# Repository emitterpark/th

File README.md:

**LoRaWAN Outdoor Temperature & Humidity Sensor**

**SENSOR**

**Temperature;**

Range -40 to +125 C

Resolution 0.01 C

Accuracy tolerance +-0.2 C

**Humidity;**

Range 0 to 100 %RH

Resolution 0.01 %RH

Accuracy tolerance +-2 %RH

High and Low Alarms with hysteresis

**RADIO**

LoRaWAN Class A

Licence Free ISM Bands (EU868, US915..), Default EU868, 8 Channel

Up to 100mW (20dbm) output power

High sensitivity -148dbm

3dbi External Antenna

Long Range, greater than 10km line of sight

**POWER**

3.6V 9000mah ER26500 C Size LiSClO2

15uA sleep current

Up to 5 years battery life depending on send interval

Low battery alarm

**CONFIGURATION**

Configuration via USB, Pc, Phone, Tablet

Send Interval, 5min to 24h

High and Low Alarm thresholds

Full LoRaWAN parameters access

Over The Air Activation (OTAA) with DevEUI, AppEUI, AppKEY

**PHYSICAL**

Outdoor IP65 waterproof enclosure

Mounting flanges

76X70X40mm

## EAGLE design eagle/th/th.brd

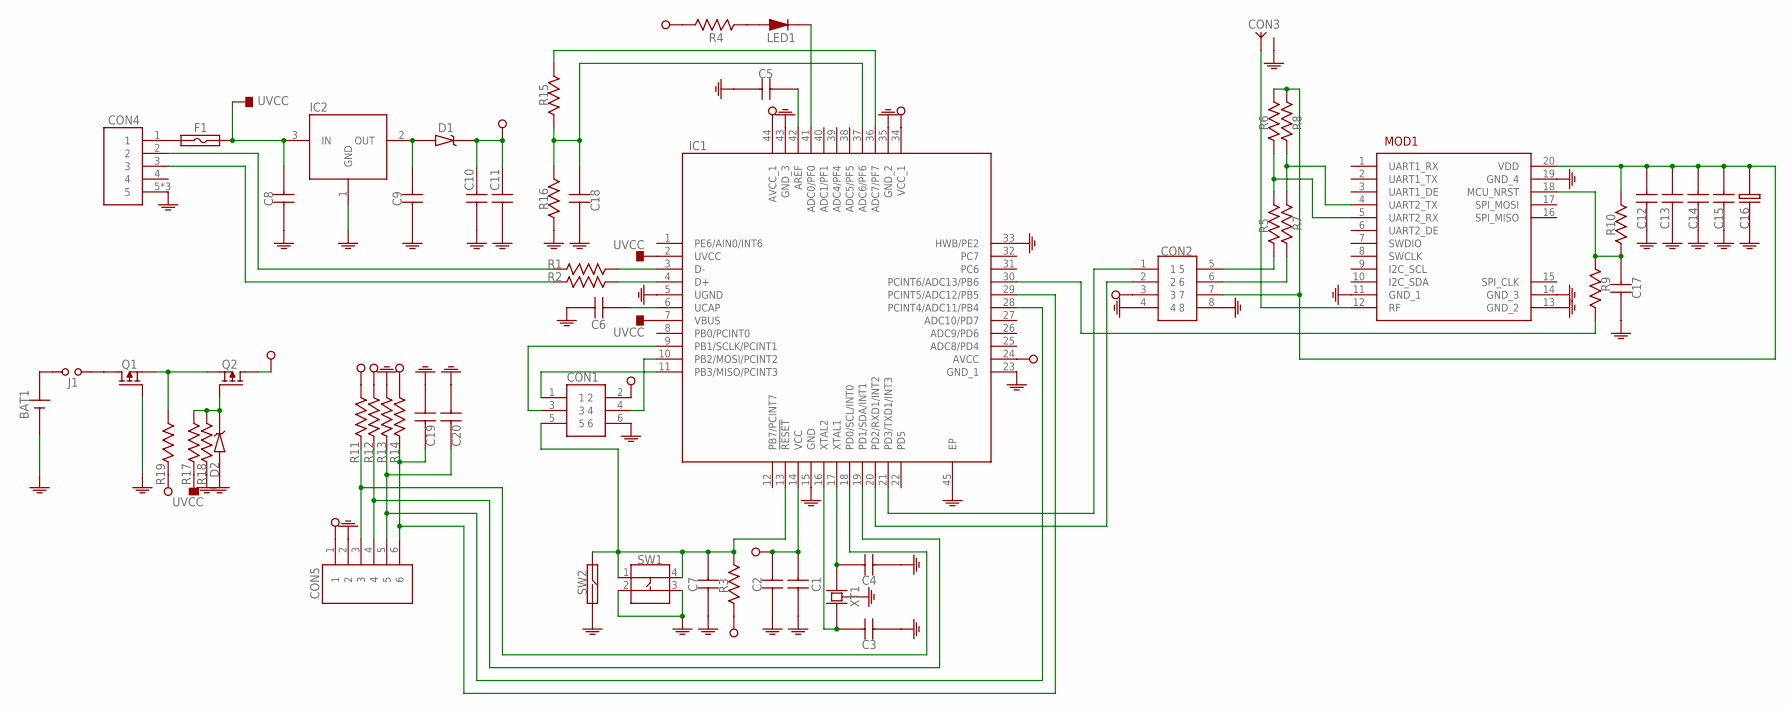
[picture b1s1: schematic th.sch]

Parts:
BAT1: 211P-C-HOLDER
C1, C2, C3, C4, C5, C6, C7, C10, C11, C12, C13, C14, C15, C17, C18, C19, C20: CAPACITOR-0603; 0603
C8, C9: CAPACITOR-0805; 0805
C16: CAPACITOR-10-5
CON1: ISP
CON2: HEADER-8P-2R-DIP-2_54MM
CON3: SMA-RF
CON4: USB-MICRO-DIP-VER
CON5: HEADER-6P-DIP-2_54MM
D1: DIODE-SCHOTTKY; SOD123-DIODE
D2: ZENER-SOD123; SOD123-DIODE
F1: FUSE-1206; 1206
IC1: ATMEGA32U4-MU; QFN-44
IC2: VREG-SOT23-3; SOT23-3
J1: JUMPER; HEADER-2P-DIP-2_54MM
LED1: LED-0805; 0805-LED
MOD1: RAK4200
Q1, Q2: P-MOSFET; SOT23-3
R1, R2, R3, R4, R5, R6, R7, R8, R9, R10, R11, R12, R13, R14, R15, R16, R17, R18, R19: RESISTOR-0603; 0603
SW1: BUTTON-4P-SMD-5X5
SW2: REED-DIP
XT1: CRYSTAL-5032-4P

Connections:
GND: BAT1.2 (-), C1.1, C2.1, C3.1, C4.1, C5.1, C6.1, C7.1, C8.1, C9.1, C10.1, C11.1, C12.1, C13.1, C14.1, C15.1, C16.P$1 (1), C17.1, C18.1, C19.1, C20.1, CON1.6, CON2.4, CON2.8, CON3.2 (GND), CON3.3 (GND), CON3.4 (GND), CON3.5 (GND), CON4.5, CON4.6 (5), CON4.7 (5), CON5.2, D2.2 (A), IC1.5 (UGND), IC1.15 (GND), IC1.23 (GND_1), IC1.33 (HWB/PE2), IC1.35 (GND_2), IC1.43 (GND_3), IC1.45 (EP), IC2.1 (GND), MOD1.11 (GND_1), MOD1.13 (GND_2), MOD1.14 (GND_3), MOD1.19 (GND_4), Q1.1 (G), R13.1, R16.1, R18.1, SW1.2, SW1.3, SW2.P$2 (2), XT1.2 (GND), XT1.4 (GND)
unnamed: C7.2, CON1.5, IC1.13 (!RESET), R3.2, SW1.1, SW1.4, SW2.P$1 (1)
unnamed: C17.2, MOD1.18 (MCU_NRST), R9.1, R10.1
unnamed: CON1.1, IC1.11 (PB3/MISO/PCINT3)
unnamed: CON3.1 (ANT), MOD1.12 (RF)
unnamed: J1.1, Q1.3 (D)
unnamed: CON2.5, R5.1
unnamed: CON2.6, R7.1
unnamed: BAT1.1 (+), J1.2 (3)
unnamed: CON1.4, IC1.10 (PB2/MOSI/PCINT2)
unnamed: C3.2, IC1.16 (XTAL2), XT1.1
unnamed: CON2.2, IC1.20 (PD2/RXD1/INT2)
unnamed: C4.2, IC1.17 (XTAL1), XT1.3 (2)
unnamed: IC1.41 (ADC0/PF0), LED1.1 (K)
unnamed: C20.2, CON5.5, IC1.28 (PCINT4/ADC11/PB4), R13.2
unnamed: C9.2, D1.2 (A), IC2.2 (OUT)
unnamed: IC1.30 (PCINT6/ADC13/PB6), R9.2
unnamed: CON4.2, R1.1
unnamed: IC1.3 (D-), R1.2
unnamed: IC1.4 (D+), R2.2
unnamed: C18.2, IC1.37 (ADC6/PF6), R15.2, R16.2
unnamed: D2.1 (K), Q2.1 (G), R17.2, R18.2
unnamed: C12.2, C13.2, C14.2, C15.2, C16.P$2 (2), CON2.7, MOD1.20 (VDD), R6.2, R8.2, R10.2
unnamed: CON2.1, IC1.21 (PD3/TXD1/INT3)
unnamed: CON4.3, R2.1
unnamed: C19.2, CON5.6, IC1.29 (PCINT5/ADC12/PB5), R14.2
unnamed: Q1.2 (S), Q2.2 (S), R19.2
unnamed: MOD1.4 (UART2_TX), R7.2, R8.1
unnamed: C5.2, IC1.42 (AREF)
unnamed: MOD1.5 (UART2_RX), R5.2, R6.1
unnamed: CON4.1, F1.1
unnamed: C6.2, IC1.6 (UCAP)
unnamed: LED1.2 (A), R4.1
unnamed: IC1.36 (ADC7/PF7), R15.1
unnamed: CON1.3, IC1.9 (PB1/SCLK/PCINT1)
unnamed: CON5.3, IC1.18 (PD0/SCL/INT0), R11.2
unnamed: CON5.4, IC1.19 (PD1/SDA/INT1), R12.2
UVCC: C8.2, F1.2, IC1.2 (UVCC), IC1.7 (VBUS), IC2.3 (IN), R17.1
VCC: C1.2, C2.2, C10.2, C11.2, CON1.2, CON2.3, CON5.1, D1.1 (K), IC1.14 (VCC), IC1.24 (AVCC), IC1.34 (VCC_1), IC1.44 (AVCC_1), Q2.3 (D), R3.1, R4.2, R11.1, R12.1, R14.1, R19.1

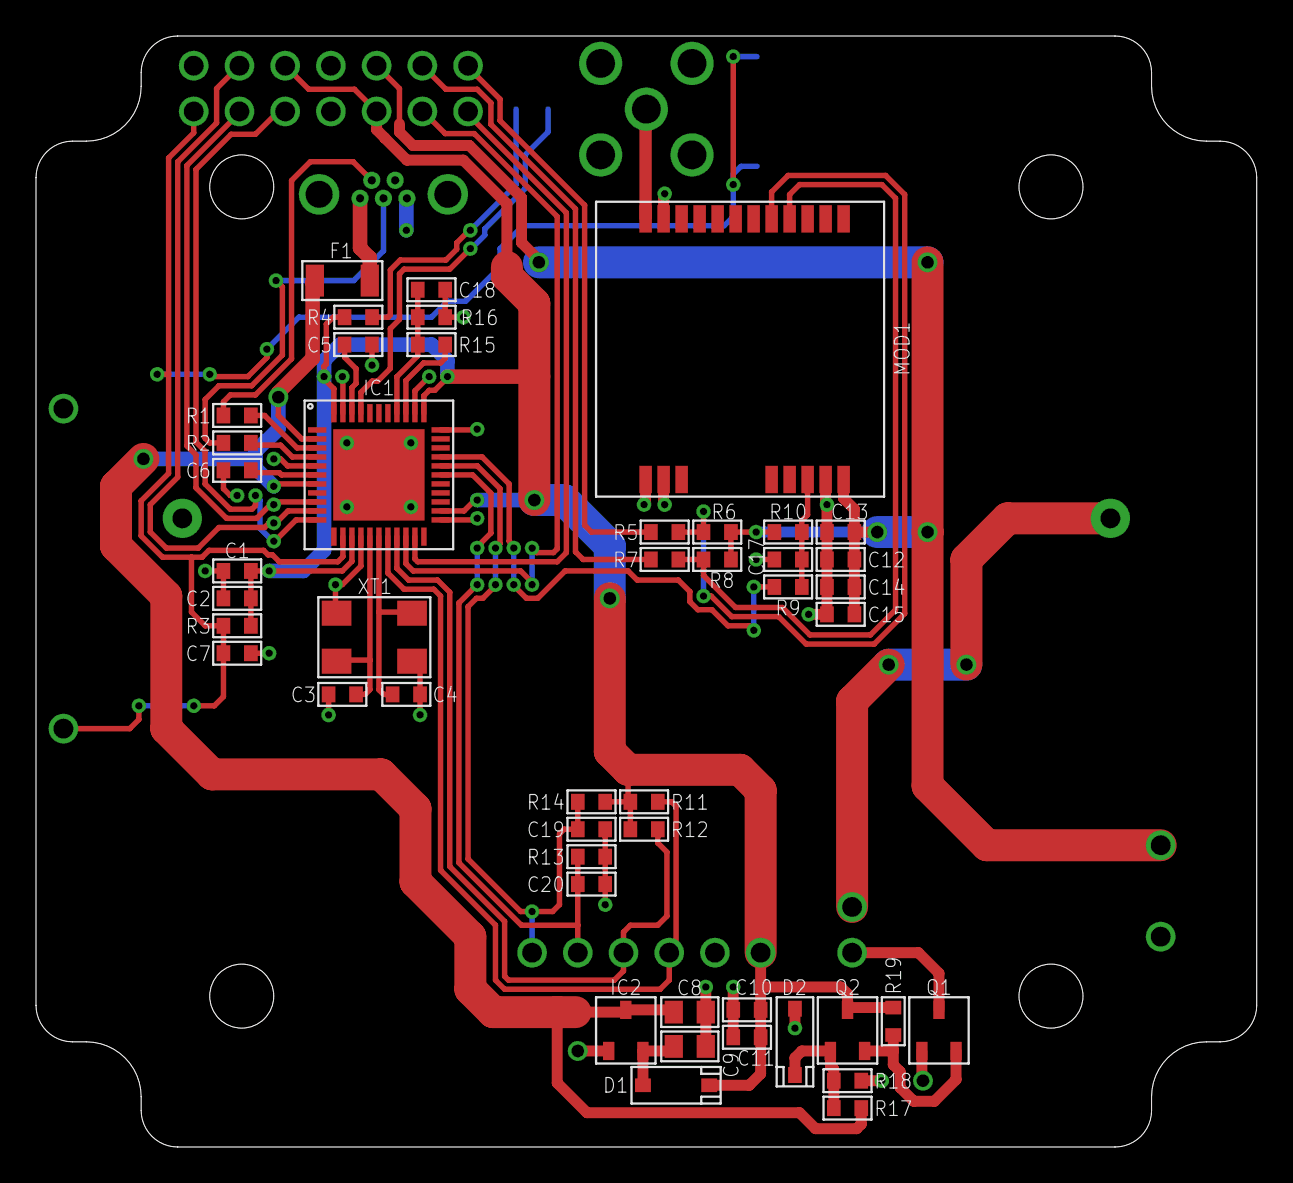
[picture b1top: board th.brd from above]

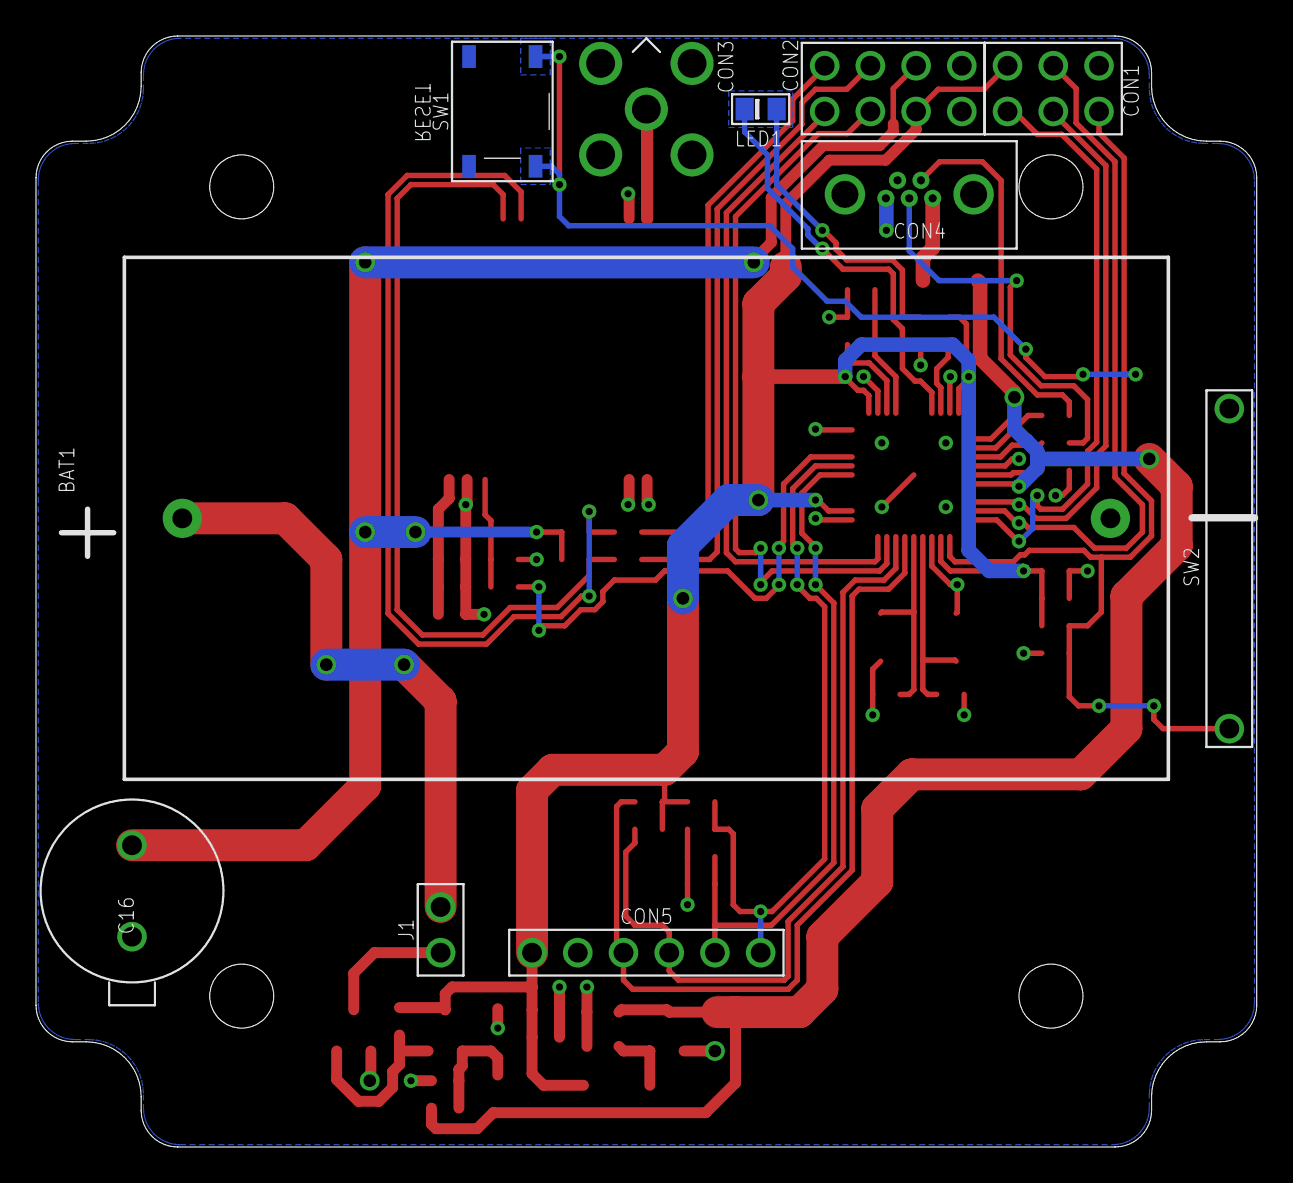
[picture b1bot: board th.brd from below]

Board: 2 copper layers, 67.8 x 61.7 mm, 58 parts (11 on the bottom side), 39 nets.

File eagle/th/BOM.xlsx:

IC1 | 1 | ATMEGA32U4-MU | QFN-44
IC2 | 1 | MCP1700T-3602E/TT | SOT23-3
MOD1 | 1 | RAK4200 LORA MODULE EU868MHZ | SM-20 | link
Q1,2 | 2 | SI2301BDS | SOT23-3
D1 | 1 | B5817W (MBR120) | SOD123
D2 | 1 | BZT52C3V9 | SOD123
LED1 | 1 | LED RED | 0805
XT1 | 1 | CRYSTAL PASSIVE 8MHZ 4PIN | 5032
F1 | 1 | PTC RESETTABLE FUSE 0.5A | 1206
SW1 | 1 | PUSH BUTTON 5.2X5.2MM 4P | SM
SW2 | 1 | REED SWITCH <=10MM NO | DIP
BAT1 | 1 | 211P-C PCB PIN C SIZE BATTERY HOLDER | DIP
CON1 | 1 | HEADER MALE 2.54MM 6P 2R | DIP
CON2 | 1 | HEADER MALE 2.54MM 8P 2R | DIP
CON3 | 1 | CONNECTOR RF SMA R/A FEMALE 20MM | DIP | link
CON4 | 1 | USB3131 MICRO B USB VERTICAL FEMALE | DIP
CON5 | 1 | HEADER FEMALE 2.54MM 6P 1R | DIP
J1 | 1 | HEADER MALE 2.54MM 2P 1R | DIP
C1,6,10,12,13 | 5 | 10UF | 0603
C2,5,7,11,14,15,17,18,19,20 | 10 | 100NF | 0603
C3,4 | 2 | 22PF | 0603
C8,9 | 2 | 10UF | 0805
C16 | 1 | 1000UF 10MM | DIP
R1,2 | 2 | 22R | 0603
R3,8,10,11,12,14,18 | 7 | 10K | 0603
R4 | 1 | 220R | 0603
R5,7,9 | 3 | 100R | 0603
R6 | 0 | NC | 0603
R13 | 1 | 1M | 0603
R15,16,17 | 3 | 1K | 0603
R19 | 1 | NC | 0603
PCB | 1 | FR4 1.6MM 67.8X61.7 MM (2670X2430 MIL)
BATTERY | 1 | ER26500 3.6V 9000MAH C SIZE LISCLO2
ANTENNA | 1 | 868MHZ 5DBI SMA-MALE WHIP |  | link
ENCLOSURE | 1 | H-393 IP65 76X70X40MM
SENSOR SHELL/COVER PLASTIC | 1 | TEMPERATURE & HUMIDITY
JUMPER | 4 | 2.54MM

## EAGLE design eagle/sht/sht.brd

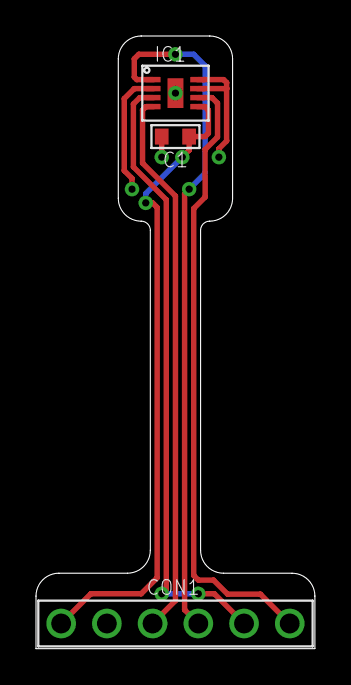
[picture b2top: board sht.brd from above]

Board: 2 copper layers, 15.5 x 34.0 mm, 3 parts (0 on the bottom side), 6 nets.

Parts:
C1: 0603
CON1: HEADER-6P-DIP-2_54MM
IC1: SHT3X-DIS

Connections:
GND: C1.1, CON1.2, IC1.2, IC1.7, IC1.8, IC1.9
unnamed: CON1.6, IC1.6
unnamed: CON1.4, IC1.1
unnamed: CON1.3, IC1.4
unnamed: CON1.5, IC1.3
VCC: C1.2, CON1.1, IC1.5

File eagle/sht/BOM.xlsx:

IC1 | 1 | SHT31-DIS-P2.5KS | DFN-8 | X
CON1 | 1 | HEADER 2.54MM 6P | DIP
C1 | 1 | 100NF | 0603 | X
PCB | 1 | FR4 1.6MM 15.5X34.0 MM (610X1340 MIL)

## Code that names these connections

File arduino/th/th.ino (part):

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#include "ClosedCube_SHT31D.h"    // https://github.com/closedcube/ClosedCube_SHT31D_Arduino
#include <WebUSB.h>               // https://github.com/webusb/arduino

const uint8_t TXD1_PIN            = 1;                // PD3/TXD1/INT3
const uint8_t AN_ALR_PIN          = 8;                // PB4/ADC11/PCINT4
const uint8_t AN_RES_PIN          = 9;                // PB5/ADC12/PCINT5
const uint8_t LORA_RES_PIN        = 10;               // PB6/ADC13/PCINT6
const uint8_t BAT_EN_PIN          = A0;               // PF7/ADC7
const uint8_t BAT_PIN             = A1;               // PF6/ADC6
const uint8_t LED_PIN             = A5;               // PF0/ADC0

const uint8_t lru08_dr            = 0;  
const uint8_t lru08_port          = 1;  
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
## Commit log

2020-06-28 init
